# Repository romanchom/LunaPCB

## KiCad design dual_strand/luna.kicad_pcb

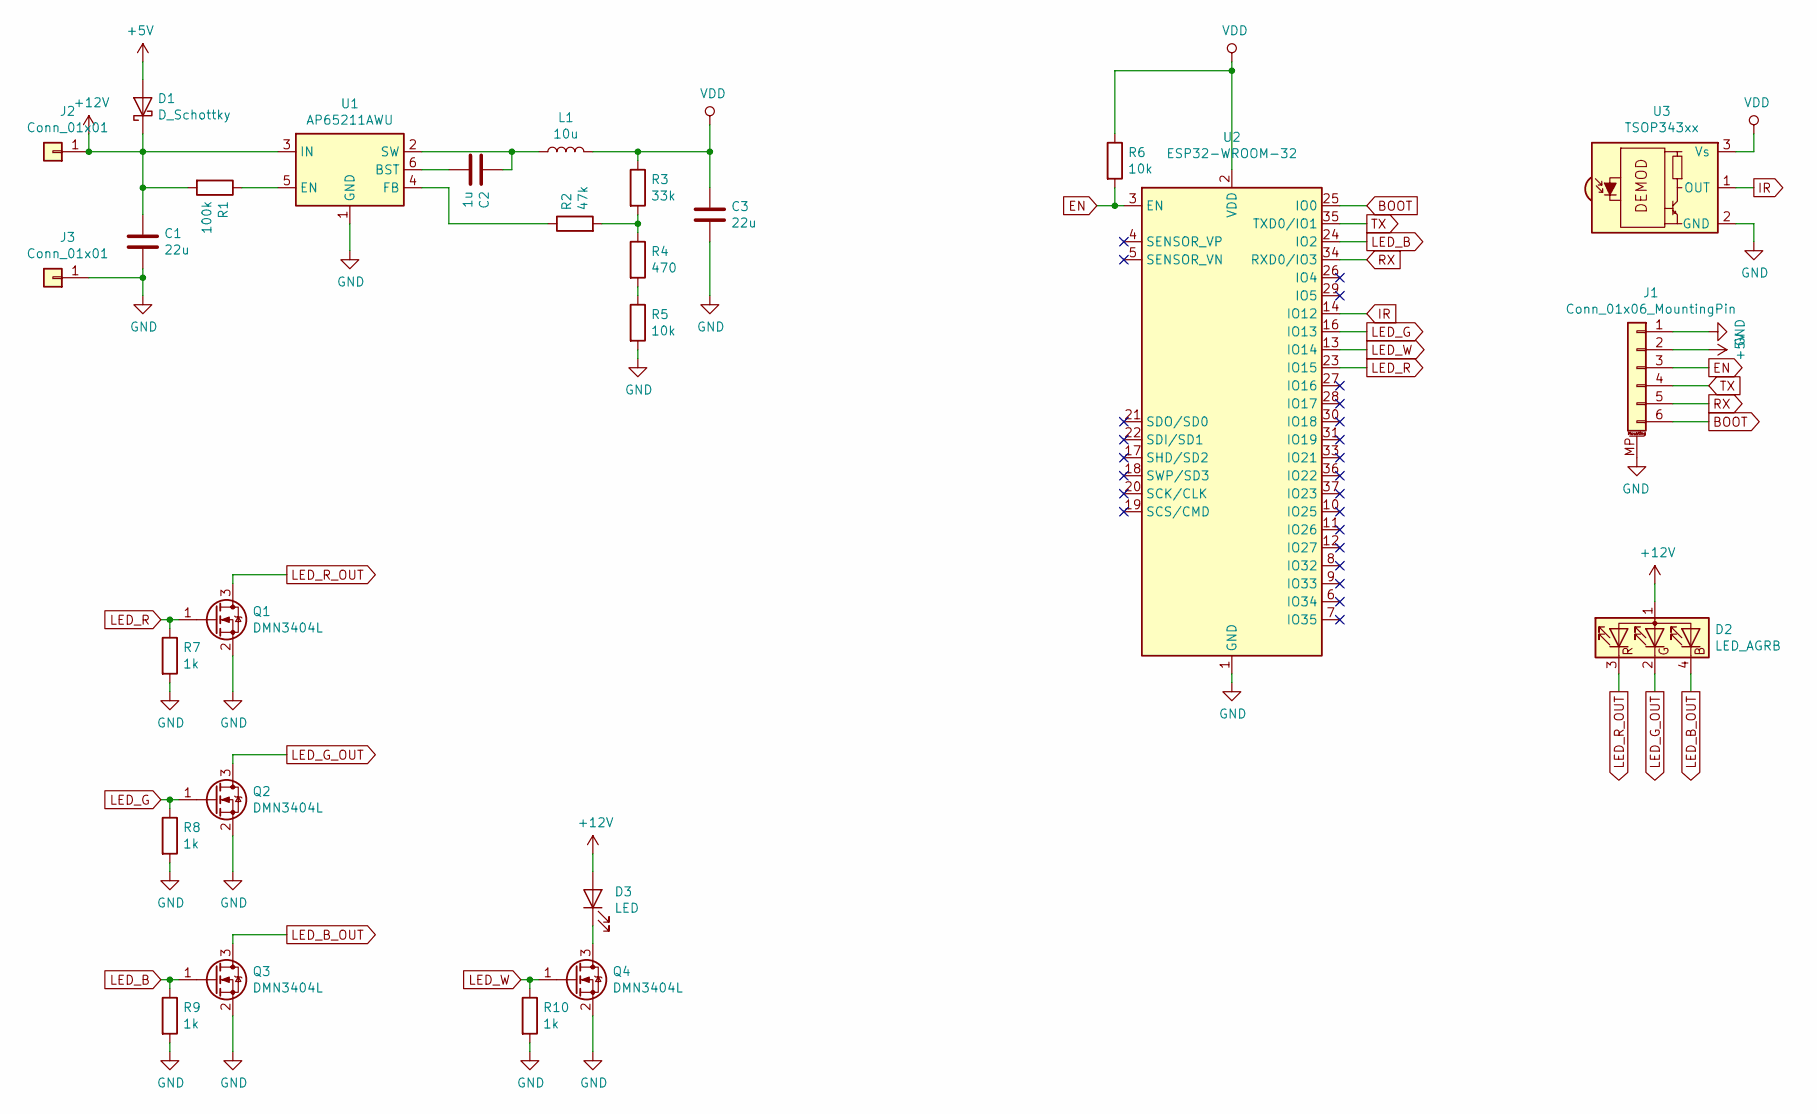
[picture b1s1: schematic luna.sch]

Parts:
C1, C3: 22u; C_1206_3216Metric_Pad1.42x1.75mm_HandSolder
C2: 1u; C_0805_2012Metric_Pad1.15x1.40mm_HandSolder
D1: D_Schottky; D_SMA
D2: LED_AGRB; LED_STRIP_RGB
D3: LED; LED_STRIP
J1: Conn_01x06_MountingPin; JST_SH_SM06B-SRSS-TB_1x06-1MP_P1.00mm_Horizontal
J2, J3: Conn_01x01; SolderWirePad_1x01_SMD_5x10mm
L1: 10u; L_Wuerth_MAPI-4020
Q1, Q2, Q3, Q4: DMN3404L; SOT-23
R1: 100k; R_0805_2012Metric_Pad1.15x1.40mm_HandSolder
R2: 47k; R_0805_2012Metric_Pad1.15x1.40mm_HandSolder
R3: 33k; R_0805_2012Metric_Pad1.15x1.40mm_HandSolder
R4: 470; R_0805_2012Metric_Pad1.15x1.40mm_HandSolder
R5, R6: 10k; R_0805_2012Metric_Pad1.15x1.40mm_HandSolder
R7, R8, R9, R10: 1k; R_0805_2012Metric_Pad1.15x1.40mm_HandSolder
U1: AP65211AWU; TSOT-23-6
U2: ESP32-WROOM-32
U3: TSOP343xx; Vishay_MOLD-3Pin

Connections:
+5V: D1.2 (A), J1.2
+12V: C1.1, D1.1 (K), D2.1 (A), D3.2 (A), J2.1, R1.2, U1.3 (IN)
BOOT: J1.6, U2.25 (IO0)
EN: J1.3, R6.2, U2.3 (EN)
GND: C1.2, C3.2, J1.1, J1.MP (MountPin), J3.1, Q1.2 (S), Q2.2 (S), Q3.2 (S), Q4.2 (S), R5.2, R7.2, R8.2, R9.2, R10.2, U1.1 (GND), U2.1 (GND), U2.15 (GND), U2.38 (GND), U2.39 (GND), U3.2 (GND)
IR: U2.14 (IO12), U3.1 (OUT)
LED_B: Q3.1 (G), R9.1, U2.24 (IO2)
LED_B_OUT: D2.4 (BK), Q3.3 (D)
LED_G: Q2.1 (G), R8.1, U2.16 (IO13)
LED_G_OUT: D2.2 (GK), Q2.3 (D)
LED_R: Q1.1 (G), R7.1, U2.23 (IO15)
LED_R_OUT: D2.3 (RK), Q1.3 (D)
LED_W: Q4.1 (G), R10.1, U2.13 (IO14)
unnamed: C2.1, L1.1, U1.2 (SW)
unnamed: C2.2, U1.6 (BST)
unnamed: D3.1 (K), Q4.3 (D)
unnamed: R1.1, U1.5 (EN)
unnamed: R2.1, U1.4 (FB)
unnamed: R2.2, R3.2, R4.1
unnamed: R4.2, R5.1
RX: J1.5, U2.34 (RXD0/IO3)
TX: J1.4, U2.35 (TXD0/IO1)
VDD: C3.1, L1.2, R3.1, R6.1, U2.2 (VDD), U3.3 (Vs)

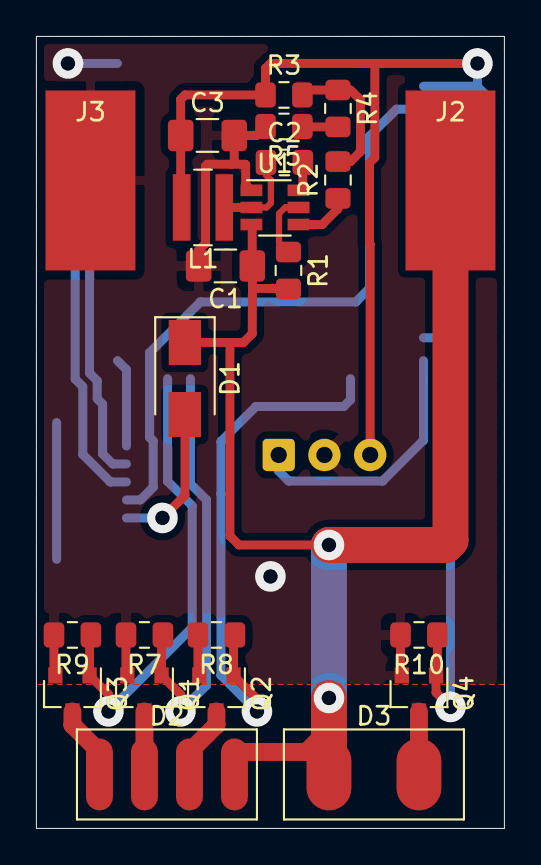
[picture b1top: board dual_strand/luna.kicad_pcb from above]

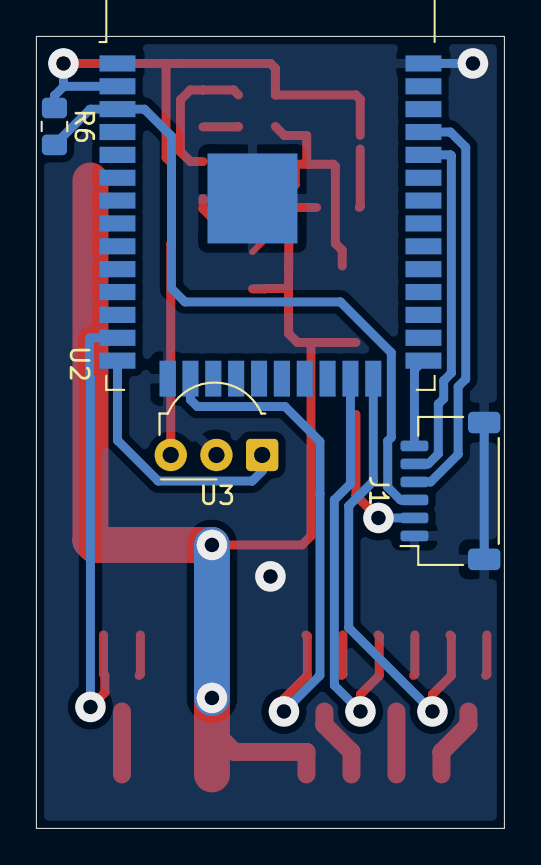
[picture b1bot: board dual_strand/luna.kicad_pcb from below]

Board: 2 copper layers, 26.0 x 44.0 mm, 27 parts (4 on the bottom side), 23 nets.

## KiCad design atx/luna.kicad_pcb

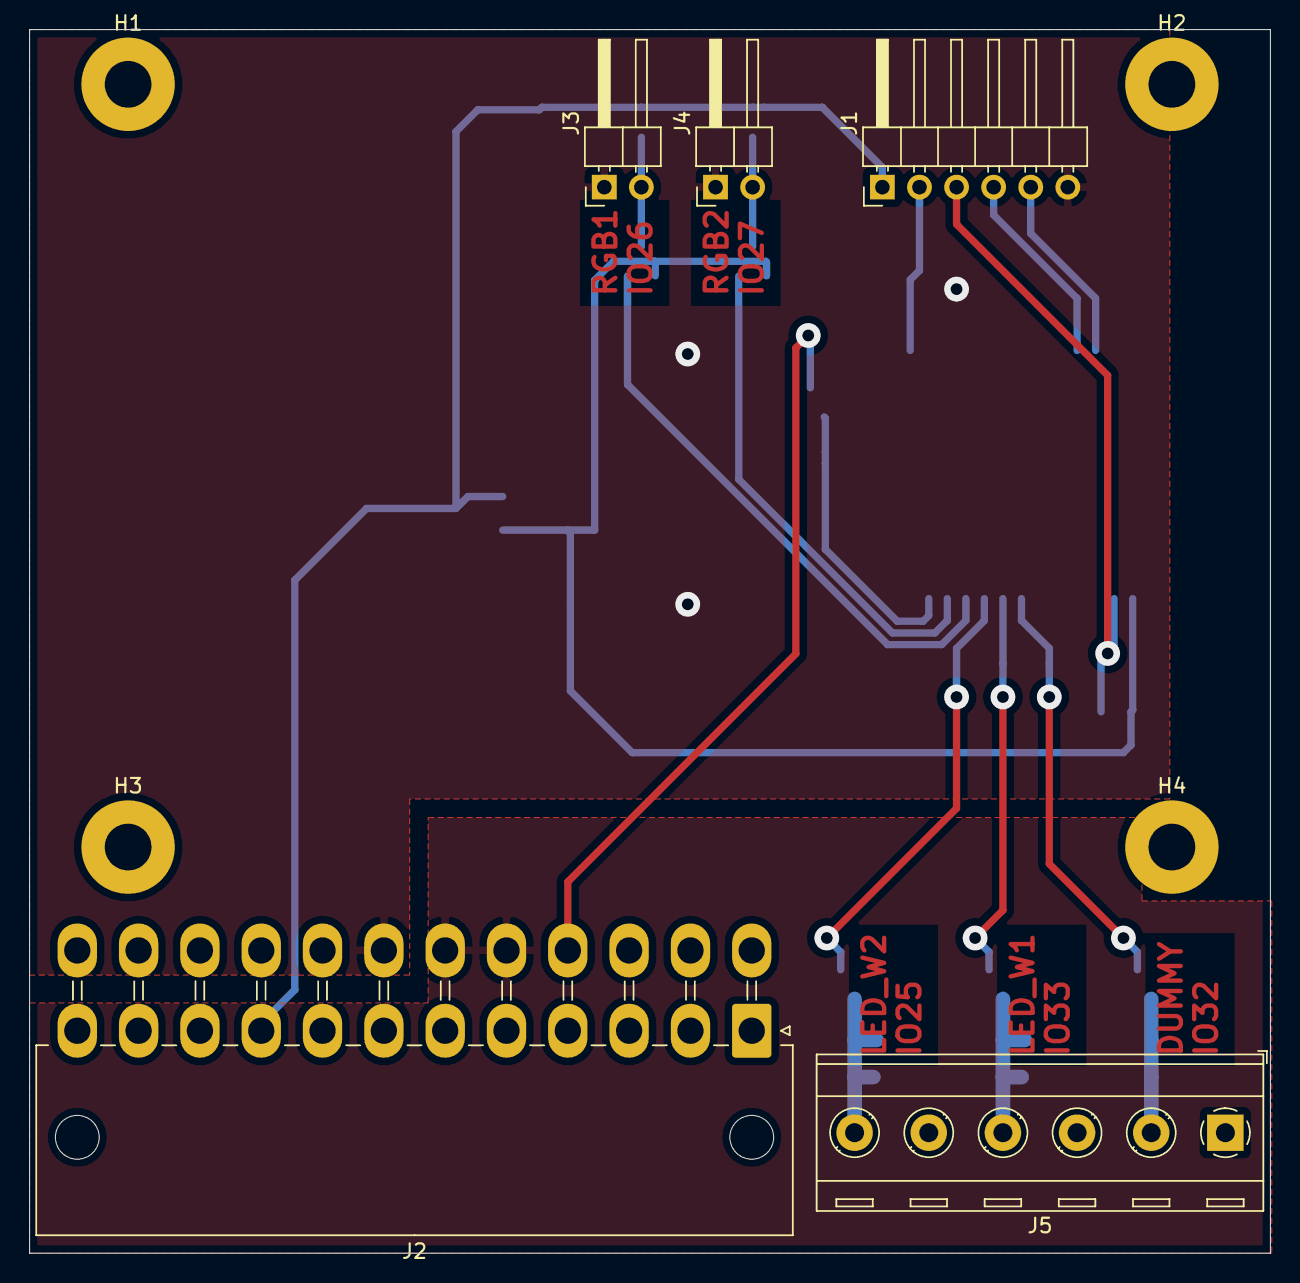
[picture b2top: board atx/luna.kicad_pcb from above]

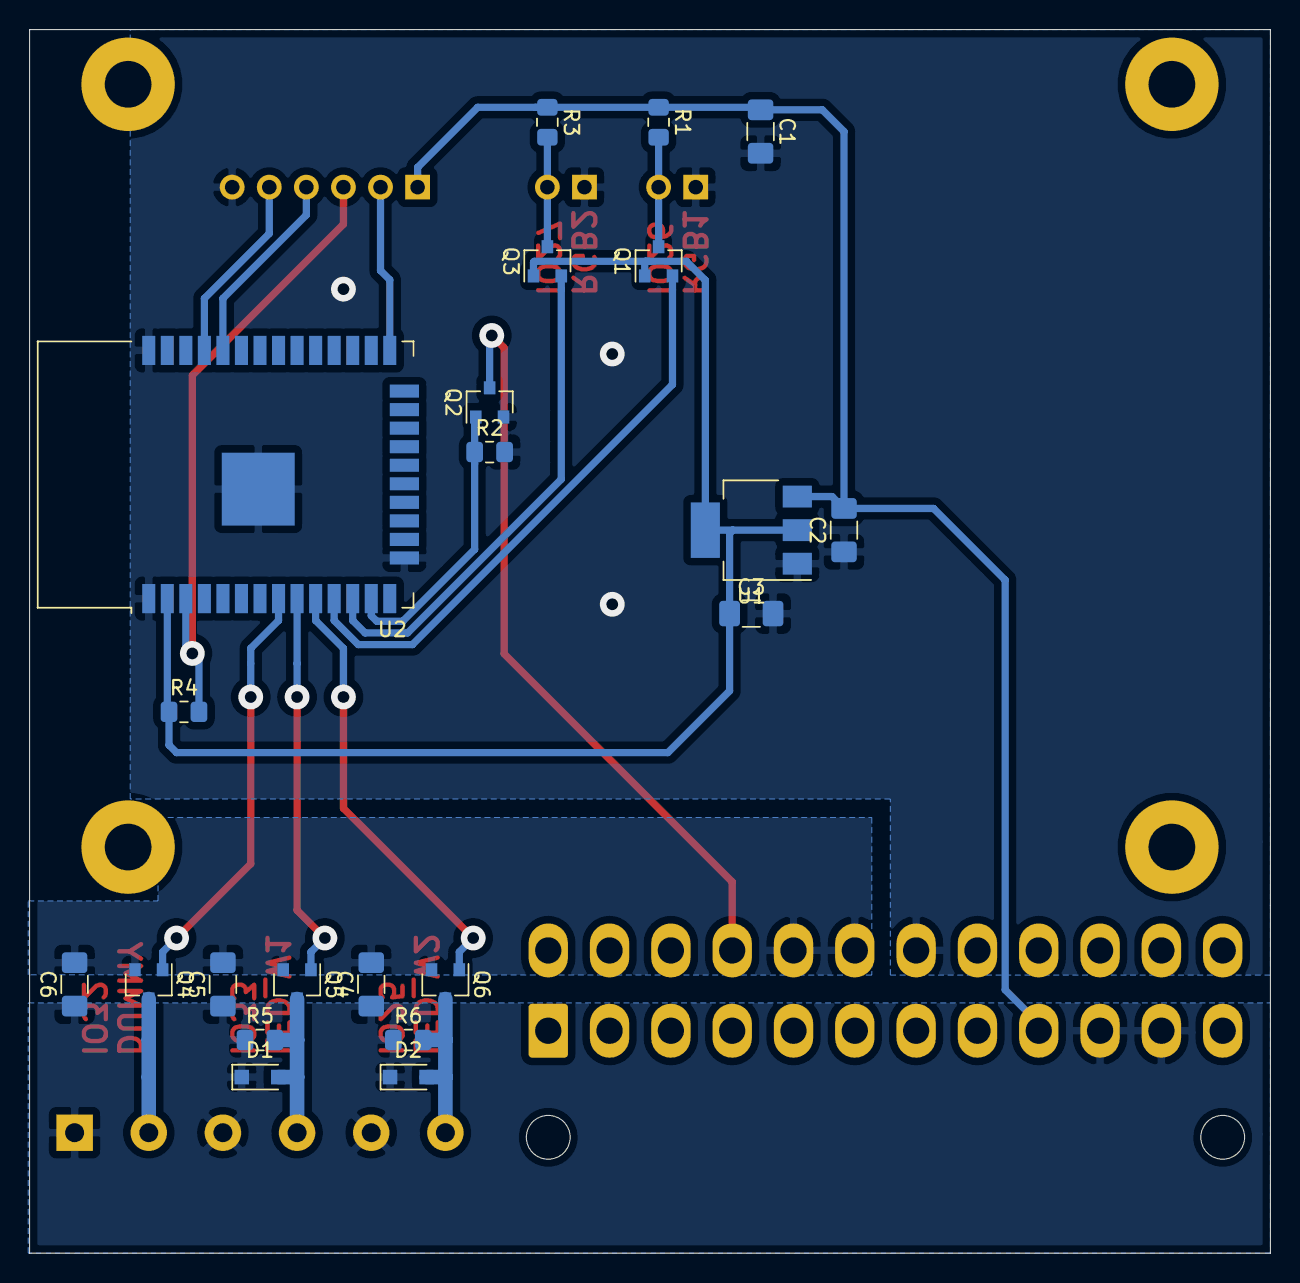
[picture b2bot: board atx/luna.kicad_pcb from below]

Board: 2 copper layers, 85.0 x 83.8 mm, 31 parts (22 on the bottom side), 21 nets.

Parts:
C1, C2, C3, C4, C5, C6: 10u; C_1206_3216Metric_Pad1.42x1.75mm_HandSolder
D1, D2: D_Schottky; D_SOD-323_HandSoldering
H1, H2, H3, H4: MountingHole_Pad; MountingHole_3.2mm_M3_Pad
J1: Conn_01x06_Male; PinHeader_1x06_P2.54mm_Horizontal
J2: Conn_02x12_Top_Bottom; Molex_Mini-Fit_Jr_5569-24A2_2x12_P4.20mm_Horizontal
J3, J4: Conn_01x02_Male; PinHeader_1x02_P2.54mm_Horizontal
J5: Screw_Terminal_01x06; TerminalBlock_RND_205-00291_1x06_P5.08mm_Horizontal
Q1, Q2, Q3: 2N7002; SOT-23
Q4, Q5, Q6: DMN3404L; SOT-23
R1, R3: 1k; R_0805_2012Metric_Pad1.15x1.40mm_HandSolder
R2, R4, R5, R6: 10k; R_0805_2012Metric_Pad1.15x1.40mm_HandSolder
U1: LD1117S33TR_SOT223; SOT-223-3_TabPin2
U2: ESP32-WROOM-32

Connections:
+5V: C1.1, C2.2, J1.1, J2.9, R1.1, R3.1, U1.3
+12V: C4.1, C5.1, C6.1, D1.1, D2.1, J2.10, J2.11, J5.1, J5.3, J5.5, R5.1, R6.1
BOOT: J1.2, U2.25
DUMMY_LOAD: Q4.1, U2.8
DUMMY_LOAD_OUT: J5.2, Q4.3
EN: J1.3, R4.2, U2.3
GND: C1.2, C2.1, C3.2, J1.6, J2.19, J3.1, J4.1, Q2.2, R2.2, U1.1, U2.1, U2.15, U2.38, U2.39
GNDPWR: C4.2, C5.2, C6.2, J2.17, J2.18, Q4.2, Q5.2, Q6.2
LED_W1: Q5.1, U2.9
LED_W1_OUT: D1.2, J5.4, Q5.3, R5.2
LED_W2: Q6.1, U2.10
LED_W2_OUT: D2.2, J5.6, Q6.3, R6.2
unnamed: J2.16, Q2.3
unnamed: J3.2, Q1.3, R1.2
unnamed: J4.2, Q3.3, R3.2
RGB1: Q1.2, U2.11
RGB2: Q3.2, U2.12
RX: J1.4, U2.34
TX: J1.5, U2.35
VDD: C3.1, Q1.1, Q3.1, R4.1, U1.2, U2.2
~ON~: Q2.1, R2.1, U2.13

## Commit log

2019-05-04 Initial commit.
2019-05-04 Almost finished.
2019-05-04 Added output pin descriptions.
2019-05-12 Second revision with on-board led swithes and dummy load output.
2019-05-14 Changed voltage regulator to LD1117. Added mounting holes to schematic. Removed flyback diode and resistor from dummy driver. Removed gate resistors.
2019-09-26 Design in progress.
2020-01-23 Finished.
2020-02-26 Removed temporary files
2020-02-26 Merged atx and compact projects
2020-02-26 Added MOSFET pull-downs. Moved IR receiver to the other side. Shrunk ground plane
